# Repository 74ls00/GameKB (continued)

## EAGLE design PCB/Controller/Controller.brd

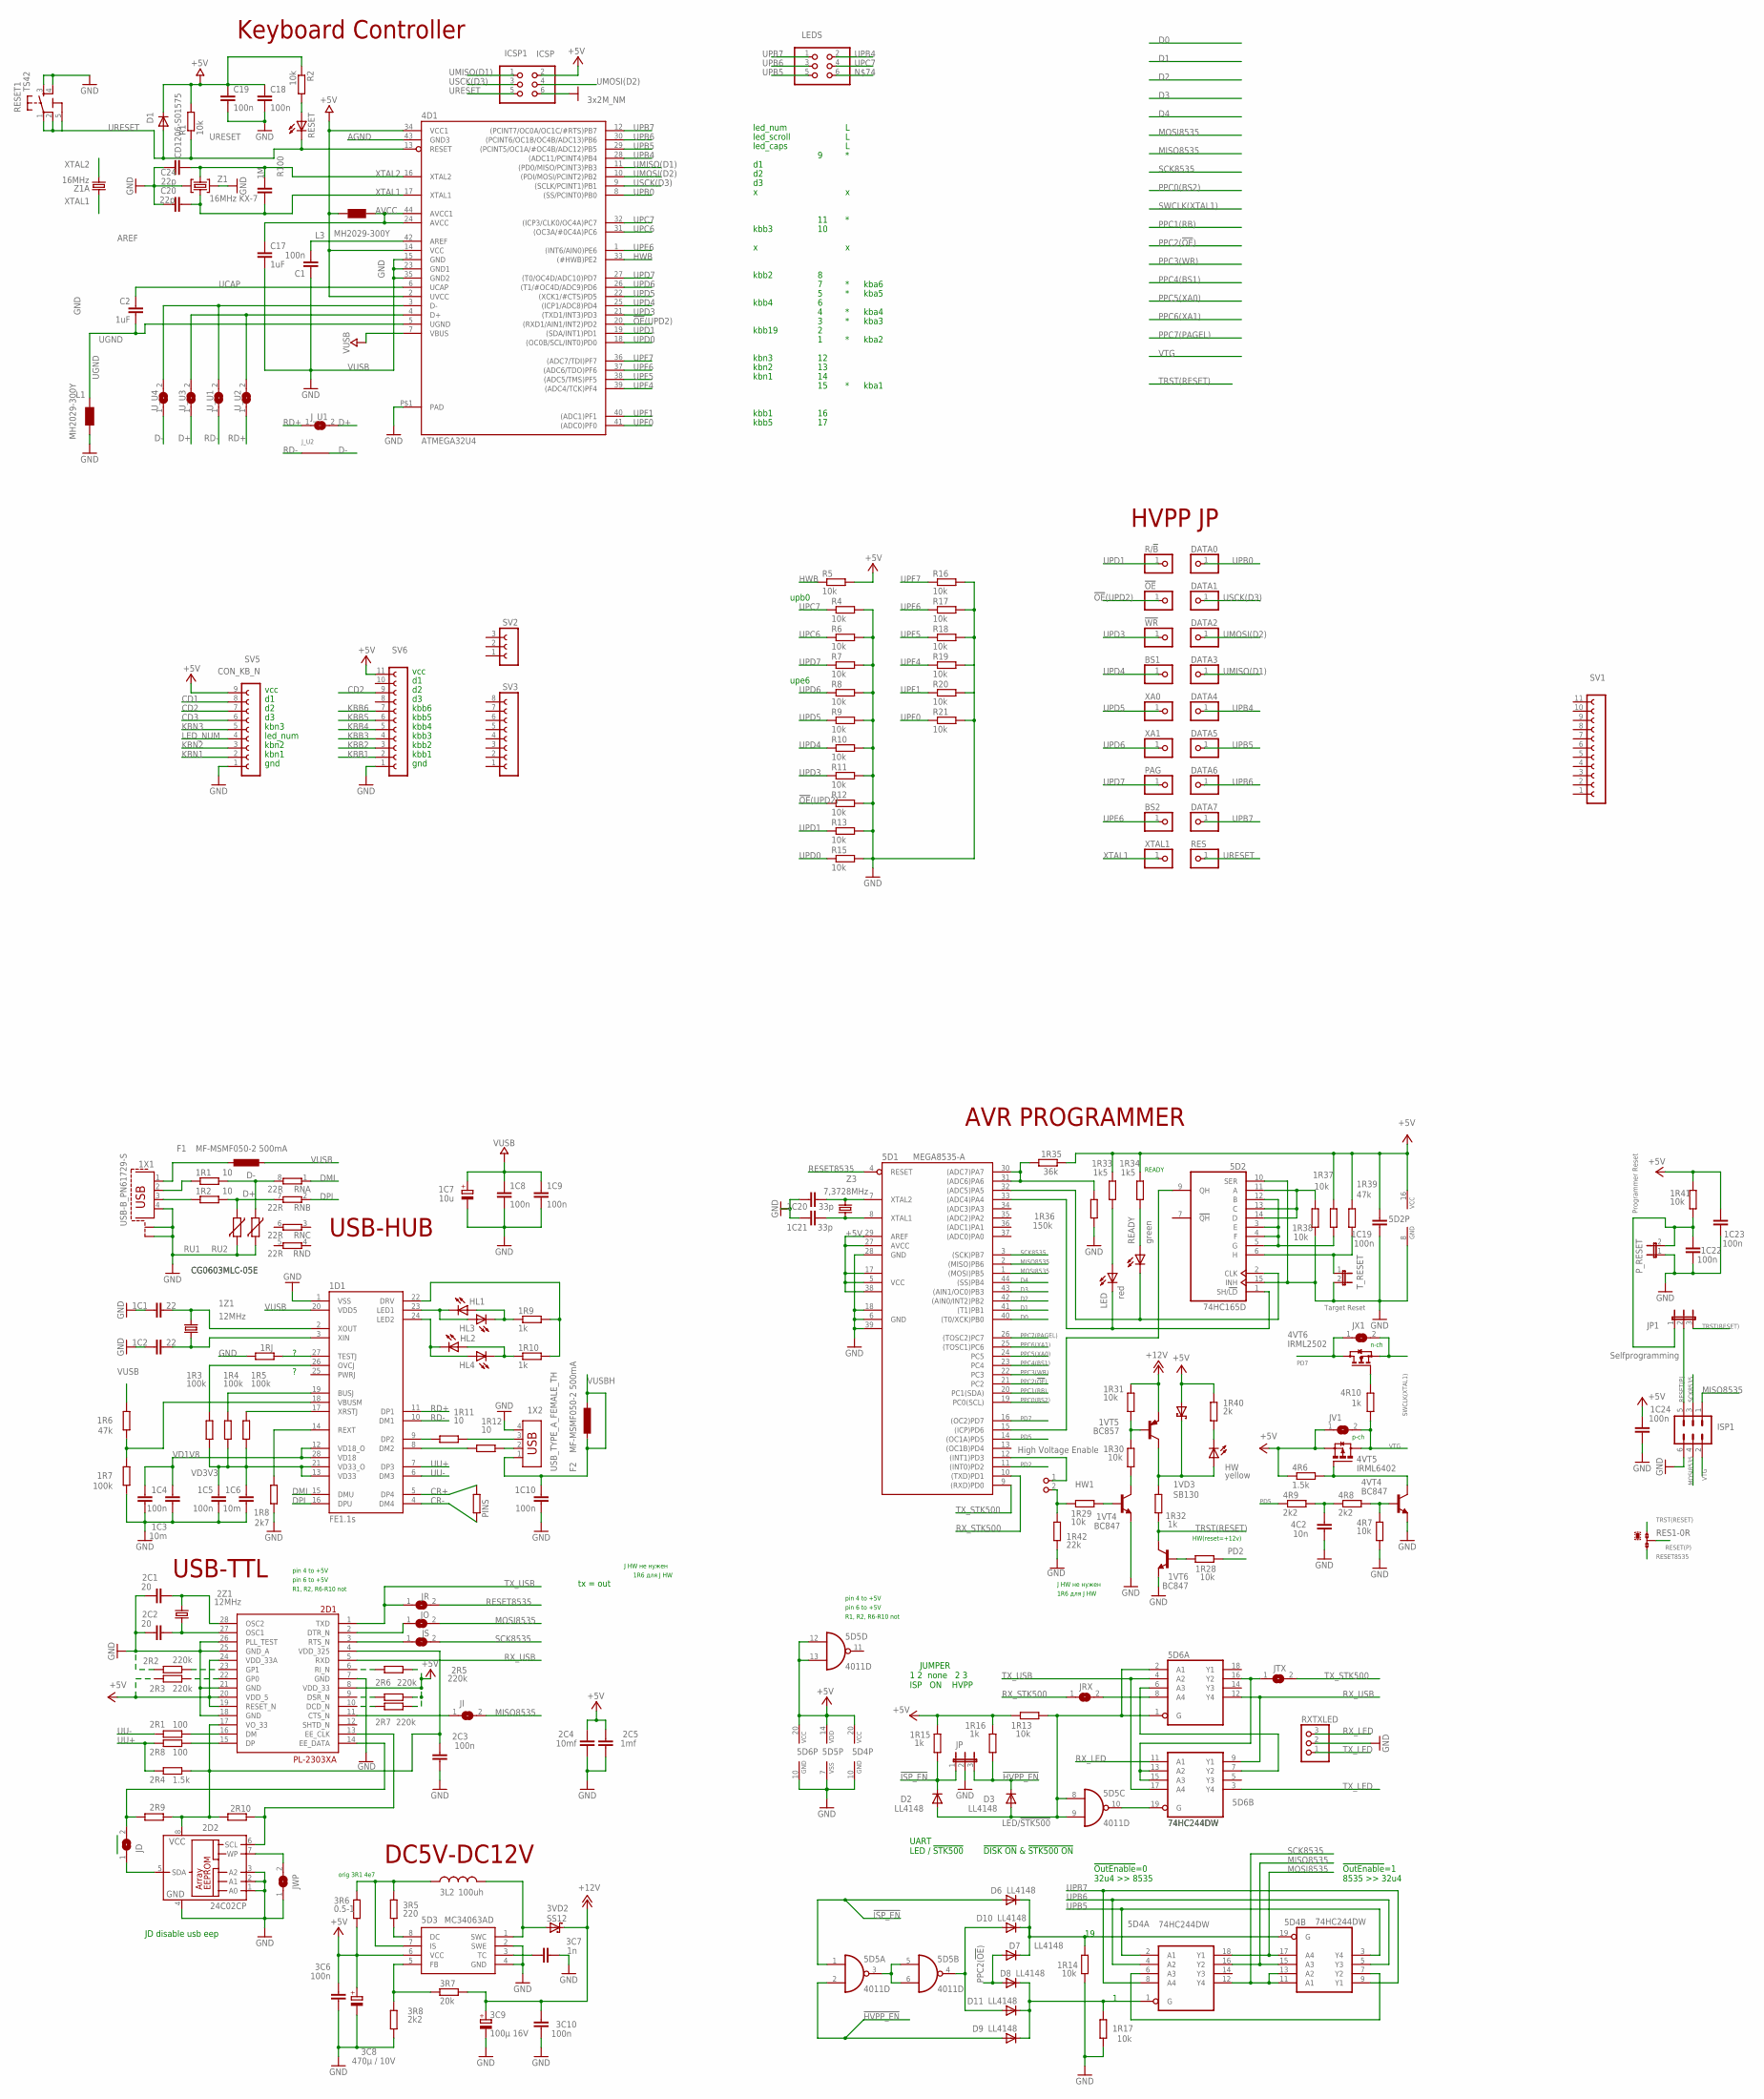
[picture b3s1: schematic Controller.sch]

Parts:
1C1, 1C2: 22; C0603
1C3, 1C6: 10m; C1206
1C4, 1C5, 1C8, 1C9, 1C10, 1C19, 1C22, 1C23, 1C24, 2C3: 100n; C0805
1C7: 10u; SMC_B
1C20, 1C21: 33p; C0805
1D1: FE1.1S; FE1.1S_SSOP-28
1R1, 1R2, 1R11, 1R12: 10; R0603
1R3, 1R4, 1R7: 100k; R0805
1R5: 100k; R1206W
1R6: 47k; R1206W
1R8: 2k7; R0805
1R9, 1R10: 1k; R0805
1R13, 1R14, 1R17, 1R29, 1R30, 1R31, 1R37, 1R38, 1R41, 4R7: 10k; M0805
1R15, 1R16, 1R32, 4R10: 1k; M0805
1R28: 10k; R0805
1R33, 1R34: 1k5; M0805
1R35: 36k; M0805
1R36: 150k; R1206
1R39: 47k; M0805
1R40: 2k; R1206W
1R42: 22k; M1206
1RJ, 2R9, 2R10: R-EU_R0805; R0805
1VD3: SB130; SMB
1VT4, 1VT6, 4VT4: BC847; SOT23
1VT5: BC857; SOT23-BEC
1X1: USB-B_PN61729-S
1X2: USB_TYPE_A_FEMALE_TH
1Z1, 2Z1: 12MHz; HC49/S
2C1, 2C2: 20; C0805
2C4: 10mf; C1210
2C5: 1mf; C0805
2D1: PL-2303XA; SSOP28DB
2D2: 24C02CP; DIL8; MPN 24C02C/P
2R1, 2R8: 100; R0603
2R2, 2R6, 2R7: 220k; R0603
2R3, 2R5: 220k; R1206W
2R4: 1.5k; R0603
3C6: 100n; C025-024X044
3C7: 1n; C025-025X050
3C8: 470µ / 10V; RCL_E3,5-8
3C9: 100µ 16V; RCL_E3,5-8
3C10: 100n; C025-025X050
3L2: 100uh; 0207/10
3R5: 220; R1206
3R6: 0.5-1; M1206
3R7: 20k; M0805
3R8, 4R9: 2k2; M0805
3VD2: SS12; SMB
4C2: 10n; C1206
4D1: ATMEGA32U4; SMARTPRJ_TQFP44-PAD
4R6: 1.5k; M0805
4R8: 2k2; M1206
4VT5: IRML6402; SUPER-SOT3
4VT6: IRML2502; SOT23
5D1: MEGA8535-A; TQFP44
5D2: 74HC165D; SO16
5D3: MC34063AD; SOIC8
5D4, 5D6: 74HC244DW; SO20W
5D5: 4011D; SO14
!OE: PINHD-1X1; 1X01
!WR: PINHD-1X1; 1X01
BS1, BS2: PINHD-1X1; 1X01
C1, C19: 100n; C0603-ROUND
C2: 1uF; C0603
C17: 1uF; C0603-ROUND
C18: 100n; C0603
C20, C24: 22p; C0603
D1: CD1206-S01575; MINIMELF
D2, D3, D6, D7, D8, D9, D10, D11: LL4148; SOD80C
DATA0, DATA1, DATA2, DATA3, DATA4, DATA5, DATA6, DATA7: PINHD-1X1; 1X01
F1, F2: MF-MSMF050-2 500mA; L1812
HL1, HL2, HL3, HL4: LEDSML0603; SML0603
HW: yellow; SML0603
HW1: High Voltage Enable; PINHEAD_1X02
ICSP1: ICSP; 2X03
ISP1: MA03-2
JD: SJ
JI: SJ
JO: SJ
JP: JP2E; JP2
JP1: Selfprogramming; JUMPER_JP2
JR: SJ
JRX: SJ
JS: SJ
JTX: SJ
JV1: SJ
JWP: SJ
JX1: SJ
J_U1: SJ
J_U2: J; R1206W
L1, L3: MH2029-300Y; 0805
LED: red; SML0603
LEDS: PINHD-2X3; 2X03
PAG: PINHD-1X1; 1X01
PINS: R-EU_R0805; R0805
P_RESET: JP1E; JP1
R1, R2, R4, R6, R7, R8, R9, R10, R11, R12, R13, R15, R16, R17, R18, R19, R20, R21: 10k; M0805
R5: 10k; M1206
R100: 1M; C0805
R/!B: PINHD-1X1; 1X01
READY: green; SML0603
RES: PINHD-1X1; 1X01
RES1: 0R-JUMPA; A0R-JMP
RESET: LEDSML0805; SML0805
RESET1: TS42
RN: 22R; CAY16
RU1, RU2: CG0603MLC-05E; CT/CN0603
RXTXLED: PINHD-1X3; 1X03
SV1, SV6: FE12-1; FE12
SV2: FE03-1
SV3: FE08-1; FE08
SV5: CON_KB_N; FE09
T_RESET: JP1E; JP1
U_U1, U_U2, U_U3, U_U4: SJ
XA0, XA1: PINHD-1X1; 1X01
XTAL1: PINHD-1X1; 1X01
Z1: 16MHz KX-7; CRYSTAL-3.2-2.5
Z1A: 16MHz; HC49/S
Z3: 7,3728MHz; HC49U-V

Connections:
3VUSB2: 2C3.1, 2D1.4 (VDD_325), 2D1.17 (VO_33), 2D2.8 (VCC), 2R4.1, 2R9.2, 2R10.2
!HVPP_EN: 1R16.1, 5D5.2 (I1), D3.C, D9.A, JP.3
!ISP_EN: 1R15.1, 5D5.1 (I0), D2.C, D6.A, JP.1
!OE741: 1R17.2, 5D4.1 (G), D8.C, D9.C, D11.C
!OE!(UPD2): 4D1.20 ((RXD1/AIN1/INT2)PD2), !OE.1, R12.1
+5V: 1C19.1, 1C23.2, 1C24.2, 1R13.2, 1R15.2, 1R16.2, 1R33.2, 1R34.2, 1R35.2, 1R37.1, 1R39.1, 1R40.2, 1R41.2, 1VD3.A, 2C4.2, 2C5.2, 2D1.8 (VDD_33), 2D1.19 (RESET_N), 2D1.20 (VDD_5), 2D1.24 (VDD_33A), 2R3.1, 2R5.2, 2R6.1, 2R7.1, 3C6.1, 3C8.+, 3R6.1, 4D1.2 (UVCC), 4D1.14 (VCC), 4D1.34 (VCC1), 4R6.1, 4VT5.2 (S), 5D1.5 (VCC), 5D1.17 (VCC1), 5D1.27 (AVCC), 5D1.29 (AREF), 5D1.38 (VCC2), 5D2.16 (VCC), 5D3.6 (VCC), 5D4.20 (VCC), 5D5.12 (I0), 5D5.13 (I1), 5D5.14 (VDD), 5D6.20 (VCC), C18.1, C19.1, D1.C, ICSP1.2, JV1.1, L3.1, R1.2, R2.1, R5.2, SV5.9, SV6.11
+12V: 1R31.2, 1VT5.E, 3C9.+, 3C10.2, 3R7.2, 3VD2.C
AGND: 4D1.43 (GND3)
AREF: 4D1.42 (AREF), C1.2
AVCC: 4D1.24 (AVCC), 4D1.44 (AVCC1), C17.1, L3.2
CD1: SV5.8
CD2: SV5.7, SV6.9
CD3: SV5.6
CR+: 1D1.5 (DP4), PINS.2
CR-: 1D1.4 (DM4), PINS.1
D0: 5D1.40 ((T0/XCK)PB0)
D1: 5D1.41 ((T1)PB1)
D2: 5D1.42 ((AIN0/INT2)PB2)
D3: 5D1.43 ((AIN1/OC0)PB3)
D4: 5D1.44 ((SS)PB4)
D+: 1R2.2, J_U1.2, RN.7 (2), RU1.1, U_U3.1
D-: 1R1.2, J_U2.1, RN.8 (2), RU2.1, U_U4.1
DMI: 1D1.15 (DMU), RN.1
DPI: 1D1.16 (DPU), RN.2 (1)
GND: 1C1.1, 1C2.1, 1C3.2, 1C4.2, 1C5.2, 1C6.2, 1C7.-, 1C8.1, 1C9.1, 1C10.2, 1C19.2, 1C20.1, 1C21.1, 1C22.1, 1C23.1, 1C24.1, 1D1.1 (VSS), 1R7.1, 1R8.1, 1R14.1, 1R17.1, 1R36.1, 1R38.1, 1R42.1, 1RJ.2, 1VT4.2 (E), 1VT6.2 (E), 1X1.4, 1X1.S1, 1X1.S2, 1X2.4, 2C1.1, 2C2.1, 2C3.2, 2C4.1, 2C5.1, 2D1.7 (GND), 2D1.18 (GND), 2D1.21 (GND), 2D1.25 (GND_A), 2D1.26 (PLL_TEST), 2D2.1 (A0), 2D2.2 (A1), 2D2.3 (A2), 2D2.4 (GND), 2R2.1, 3C6.2, 3C7.2, 3C8.-, 3C9.-, 3C10.1, 3R8.1, 4C2.1, 4D1.15 (GND), 4D1.23 (GND1), 4D1.35 (GND2), 4D1.P$1 (PAD), 4R7.1, 4VT4.2 (E), 5D1.6 (GND), 5D1.18 (GND1), 5D1.28 (GND), 5D1.39 (GND2), 5D2.8 (GND), 5D2.10 (SER), 5D2.15 (INH), 5D3.2 (SWE), 5D3.4 (GND), 5D4.10 (GND), 5D5.7 (VSS), 5D6.10 (GND), C1.1, C17.2, C18.2, C19.2, C20.1, C24.2, ICSP1.6, ISP1.6, JP.2, JWP.1, L1.2, P_RESET.1, R4.2, R6.2, R7.2, R8.2, R9.2, R10.2, R11.2, R12.2, R13.2, R15.2, R16.2, R17.2, R18.2, R19.2, R20.2, R21.2, RESET1.3, RESET1.4, RU1.2, RU2.2, RXTXLED.2, SV5.1, SV6.1, T_RESET.2, Z1.2 (GND), Z1.4 (GND)
HWB: 4D1.33 ((#HWB)PE2), R5.1
ID+: 1R2.1, 1X1.3
ID-: 1R1.1, 1X1.2
KBB1: SV6.2
KBB2: SV6.3
KBB3: SV6.4
KBB4: SV6.5
KBB5: SV6.6
KBB6: SV6.7
KBN1: SV5.2
KBN2: SV5.3
KBN3: SV5.5
LED/!STK500: 1R13.1, 5D5.8 (I0), 5D5.9 (I1), 5D6.1 (G), 5D6.2 (A1), D2.A, D3.A
LED_NUM: SV5.4
MISO8535: 5D1.2 ((MISO)PB6), 5D4.15 (A3), 5D4.16 (Y2), ISP1.1, JI.2
MOSI8535: 5D1.1 ((MOSI)PB5), 5D4.17 (A4), 5D4.18 (Y1), ISP1.4, JO.2
N1: 5D1.33 ((ADC4)PA4), 5D2.1 (SH/!LD), LED.C
unnamed: 5D5.10 (O), 5D6.19 (G)
unnamed: R2.2, RESET.A
unnamed: 5D4.6 (A3), 5D4.7 (Y2)
unnamed: 1D1.9 (DP2), 1R11.1
unnamed: 1D1.8 (DM2), 1R12.1
unnamed: 1X1.1, F1.2
unnamed: 1C1.2, 1D1.2 (XOUT), 1Z1.1
unnamed: 1C2.2, 1D1.3 (XIN), 1Z1.2
unnamed: 1D1.17 (XRSTJ), 1R5.2
unnamed: 1D1.22 (DRV), 1R9.2, 1R10.2
unnamed: 1R11.2, 1X2.3
unnamed: 1R12.2, 1X2.2
unnamed: 1D1.23 (LED1), HL1.C, HL3.A
unnamed: 1D1.19 (BUSJ), 1R4.2
unnamed: 1D1.18 (VBUSM), 1R6.1, 1R7.2
unnamed: 1D1.24 (LED2), HL2.C, HL4.A
unnamed: 1R10.1, HL2.A, HL4.C
unnamed: 1D1.26 (OVCJ), 1R3.2
unnamed: 4D1.4 (D+), U_U2.2, U_U3.2
unnamed: 1D1.14 (REXT), 1R8.2
unnamed: 5D6.13 (A2), 5D6.15 (A3), 5D6.16 (Y2), JTX.1
unnamed: 1D1.27 (TESTJ), 1RJ.1
unnamed: 5D6.8 (A4), JRX.2
unnamed: 4D1.3 (D-), U_U1.2, U_U4.2
unnamed: 5D6.6 (A3), 5D6.7 (Y2)
unnamed: 2D2.5 (SDA), JD.1
unnamed: 1R34.1, READY.A
unnamed: 5D5.3 (O), 5D5.5 (I0), 5D5.6 (I1)
unnamed: 1R9.1, HL1.A, HL3.C
unnamed: 1R35.1, 1R36.2, 5D1.30 ((ADC7)PA7), 5D1.31 ((ADC6)PA6)
unnamed: 5D1.32 ((ADC5)PA5), 5D2.2 (CLK), READY.C
unnamed: 1R39.2, 5D2.6 (H), T_RESET.1
unnamed: 5D1.12 ((INT1)PD3), HW1.1
unnamed: 1R29.2, 1R42.2, HW1.2
unnamed: 2D2.7 (WP), JWP.2
unnamed: 1R32.2, 1VD3.C, 1VT5.C, HW.A
unnamed: 1R29.1, 1VT4.1 (B)
unnamed: 1R14.2, 5D4.19 (G), D6.C, D7.C, D10.C
unnamed: 1R30.1, 1VT4.3 (C)
unnamed: 1R30.2, 1R31.1, 1VT5.B
unnamed: 5D1.15 ((ICP)PD6), 5D2.9 (QH)
unnamed: 1R33.1, LED.A
unnamed: 1R38.2, 5D2.11 (A), 5D2.13 (C), 5D2.14 (D)
unnamed: 2D1.15 (DP), 2R8.2
unnamed: 2D1.16 (DM), 2R1.2
unnamed: 2D1.23 (GP1), 2R2.2
unnamed: 2D1.22 (GP0), 2R3.2
unnamed: 2C1.2, 2D1.28 (OSC2), 2Z1.2
unnamed: 2C2.2, 2D1.27 (OSC1), 2Z1.1
unnamed: 2D1.6 (RI_N), 2R5.1
unnamed: 2D1.9 (DSR_N), 2R6.2
unnamed: 2D1.10 (DCD_N), 2R7.2
unnamed: 2D1.11 (CTS_N), JI.1
unnamed: 2D1.3 (RTS_N), JS.1
unnamed: 2D1.2 (DTR_N), JO.1
unnamed: 1R37.2, 5D2.3 (E), 5D2.4 (F), 5D2.5 (G), 5D2.12 (B)
unnamed: 2D1.14 (EE_DATA), 2R9.1, JD.2
unnamed: 2D1.13 (EE_CLK), 2D2.6 (SCL), 2R10.1
unnamed: 1R28.2, 1VT6.1 (B)
unnamed: 3R5.1, 5D3.8 (DC)
unnamed: 3L2.1, 3R5.2, 3R6.2, 5D3.7 (IS)
unnamed: 5D5.4 (O), D10.A, D11.A
unnamed: 3R7.1, 3R8.2, 5D3.5 (FB)
unnamed: 3L2.2, 3VD2.A, 5D3.1 (SWC)
unnamed: 3C7.1, 5D3.3 (TC)
unnamed: 1C20.2, 5D1.7 (XTAL2), Z3.2
unnamed: 1C21.2, 5D1.8 (XTAL1), Z3.1
unnamed: 4R6.2, 4VT4.3 (C), 4VT5.1 (G)
unnamed: 4R7.2, 4R8.2, 4VT4.1 (B)
unnamed: 4C2.2, 4R8.1, 4R9.2
unnamed: 1R40.1, HW.C
unnamed: 4R10.2, 4VT6.1 (G)
PD2: 1R28.1, 5D1.11 ((INT0)PD2)
PD5: 4R9.1, 5D1.14 ((OC1A)PD5)
PD7: 4VT6.3 (D), 5D1.16 ((OC2)PD7), JX1.1
PPC0(BS2): 5D1.19 (PC0(SCL))
PPC1(RB): 5D1.20 (PC1(SDA))
PPC2(!OE!): 5D1.21 (PC2), D7.A, D8.A
PPC3(WR): 5D1.22 (PC3)
PPC4(BS1): 5D1.23 (PC4)
PPC5(XA0): 5D1.24 (PC5)
PPC6(XA1): 5D1.25 ((TOSC1)PC6)
PPC7(PAGEL): 5D1.26 ((TOSC2)PC7)
RD+: 1D1.11 (DP1), J_U1.1, U_U2.1
RD-: 1D1.10 (DM1), J_U2.2, U_U1.1
RESET8535: 1C22.2, 1R41.1, 5D1.4 (RESET), JP1.1, JR.2, P_RESET.2, RES1.3
RESET(P): ISP1.5, JP1.2, RES1.2
RX_LED: 5D6.11 (A1), RXTXLED.3
RX_STK500: 5D1.10 ((TXD)PD1), JRX.1
RX_USB: 2D1.5 (RXD), 5D6.9 (Y1), 5D6.12 (Y4)
SCK8535: 5D1.3 ((SCK)PB7), 5D4.11 (A1), 5D4.12 (Y4), 5D4.13 (A2), ISP1.3, JS.2
SWCLK(XTAL1): 4VT6.2 (S), JX1.2
TRST(RESET): 1R32.1, 1VT6.3 (C), JP1.3, RES1.1
TX_LED: 5D6.3 (Y4), RXTXLED.1
TX_STK500: 5D1.9 ((RXD)PD0), JTX.2
TX_USB: 2D1.1 (TXD), 5D6.4 (A2), 5D6.17 (A4), JR.1
UCAP: 4D1.6 (UCAP), C2.1
UGND: 4D1.5 (UGND), C2.2, L1.1
UMISO(D1): 4D1.11 ((PD0/MISO/PCINT3)PB3), DATA3.1, ICSP1.1
UMOSI(D2): 4D1.10 ((PDI/MOSI/PCINT2)PB2), DATA2.1, ICSP1.4
UPB0: 4D1.8 ((SS/PCINT0)PB0), DATA0.1
UPB4: 4D1.28 ((ADC11/PCINT4)PB4), DATA4.1, LEDS.2
UPB5: 4D1.29 ((PCINT5/OC1A/#OC4B/ADC12)PB5), 5D4.2 (A1), 5D4.3 (Y4), DATA5.1, LEDS.5
UPB6: 4D1.30 ((PCINT6/OC1B/OC4B/ADC13)PB6), 5D4.4 (A2), 5D4.5 (Y3), DATA6.1, LEDS.3
UPB7: 4D1.12 ((PCINT7/OC0A/OC1C/#RTS)PB7), 5D4.8 (A4), 5D4.9 (Y1), DATA7.1, LEDS.1
UPC6: 4D1.31 ((OC3A/#0C4A)PC6), R6.1
UPC7: 4D1.32 ((ICP3/CLK0/OC4A)PC7), LEDS.4, R4.1
UPD0: 4D1.18 ((OC0B/SCL/INT0)PD0), R15.1
UPD1: 4D1.19 ((SDA/INT1)PD1), R13.1, R/!B.1
UPD3: 4D1.21 ((TXD1/INT3)PD3), !WR.1, R11.1
UPD4: 4D1.25 ((ICP1/ADC8)PD4), BS1.1, R10.1
UPD5: 4D1.22 ((XCK1/#CTS)PD5), R9.1, XA0.1
UPD6: 4D1.26 ((T1/#OC4D/ADC9)PD6), R8.1, XA1.1
UPD7: 4D1.27 ((T0/OC4D/ADC10)PD7), PAG.1, R7.1
UPE6: 4D1.1 ((INT6/AIN0)PE6), BS2.1
UPF0: 4D1.41 ((ADC0)PF0), R21.1
UPF1: 4D1.40 ((ADC1)PF1), R20.1
UPF4: 4D1.39 ((ADC4/TCK)PF4), R19.1
UPF5: 4D1.38 ((ADC5/TMS)PF5), R18.1
UPF6: 4D1.37 ((ADC6/TDO)PF6), R17.1
UPF7: 4D1.36 ((ADC7/TDI)PF7), R16.1
URESET: 4D1.13 (RESET), D1.A, ICSP1.5, R1.1, RES.1, RESET.C, RESET1.1, RESET1.2, RESET1.5 (5-GND)
USCK(D3): 4D1.9 ((SCLK/PCINT1)PB1), DATA1.1, ICSP1.3
UU+: 1D1.7 (DP3), 2R4.2, 2R8.1
UU-: 1D1.6 (DM3), 2R1.1
VD1V8: 1C3.1, 1C4.1, 1D1.12 (VD18_O), 1D1.28 (VD18)
VD3V3: 1C5.1, 1C6.1, 1D1.13 (VD33), 1D1.21 (VD33_O), 1R3.1, 1R4.1, 1R5.1
VTG: 4R10.1, 4VT5.3 (D), ISP1.2, JV1.2
VUSB: 1C7.+, 1C8.2, 1C9.2, 1D1.20 (VDD5), 1R6.2, 4D1.7 (VBUS), F1.1
VUSBH: 1C10.1, 1X2.1, F2.1, F2.2
XTAL1: 4D1.17 (XTAL1), C20.2, R100.2, XTAL1.1, Z1.3 (C2), Z1A.2
XTAL2: 4D1.16 (XTAL2), C24.1, R100.1, Z1.1 (C1), Z1A.1

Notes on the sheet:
kbn1
kbn2
kbn3
led_num
kbb1
kbb2
kbb3
kbb4
kbb5
kbb6
gnd
vcc
pin 4 to +5V
R1, R2, R6-R10 not
pin 6 to +5V
J HW не нужен
1R6 для J HW
USB-HUB
kbb19
led_caps
led_scroll
USB-TTL
Target Reset
Programmer Reset
orig 3R1 4e7
HW(reset=+12v)
READY
n-ch
p-ch
HVPP JP
upe6
upb0
kba1
kba2
kba3
kba4
kba5
kba6
DC5V-DC12V
!DISK ON! & !STK500 ON

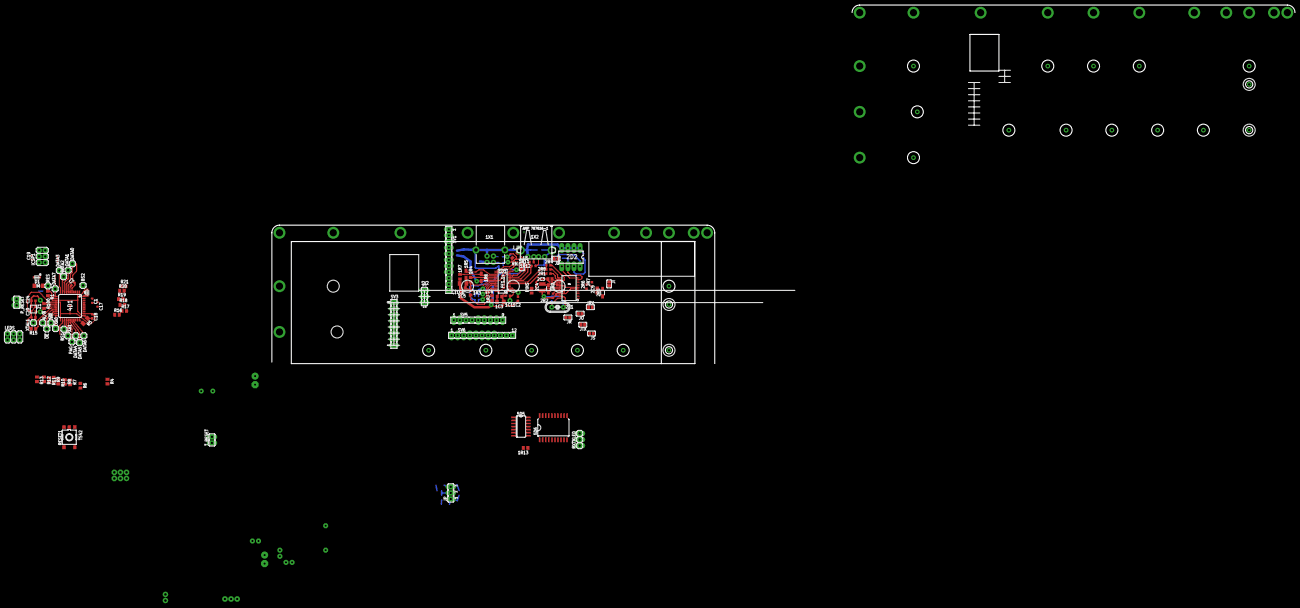
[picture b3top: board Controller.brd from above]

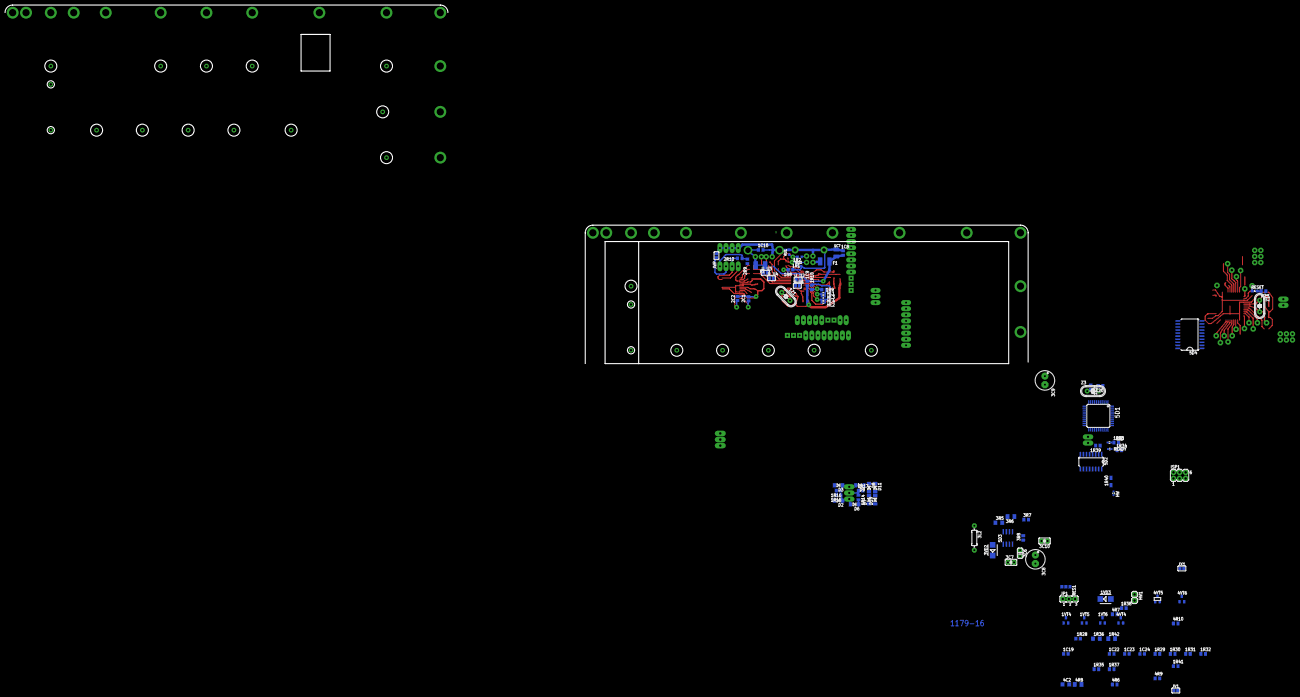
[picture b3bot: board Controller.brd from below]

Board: 2 copper layers, 208 parts (94 on the bottom side), 149 nets.

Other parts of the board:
U$3: U235

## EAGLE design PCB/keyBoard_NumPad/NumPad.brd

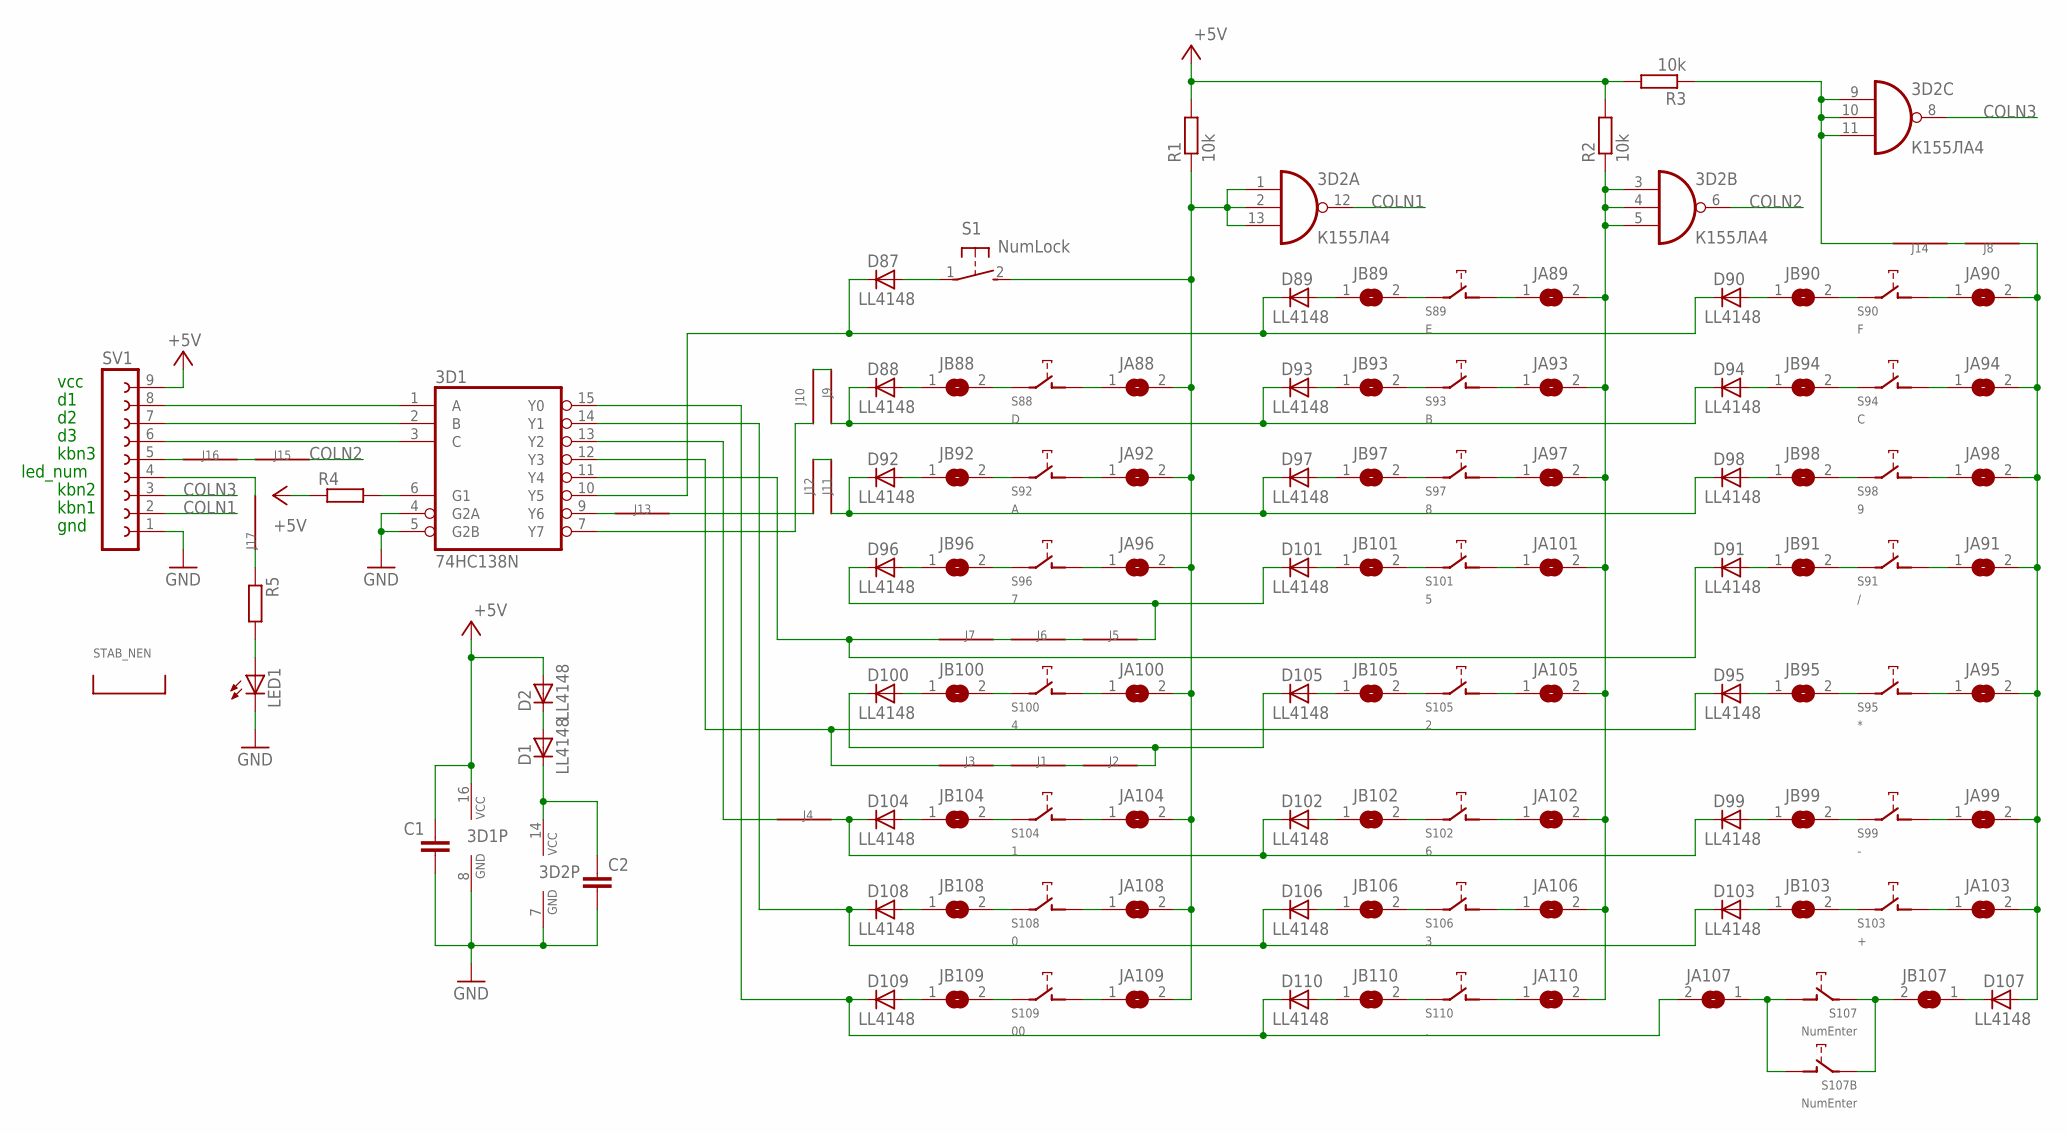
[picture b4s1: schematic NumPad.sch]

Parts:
3D1: 74HC138N; DIL16
3D2: К155ЛА4; DIL14
C1, C2: C-EUC1206; C1206
D1, D2, D87, D88, D89, D90, D91, D92, D93, D94, D95, D96, D97, D98, D99, D100, D101, D102, D103, D104, D105, D106, D107, D108, D109, D110: LL4148; SOD80C
J1, J2, J3, J4, J5, J6, J7, J8, J9, J10, J11, J12, J13, J14, J15, J16, J17: J; R1206W
JA88, JA89, JA90, JA91, JA92, JA93, JA94, JA95, JA96, JA97, JA98, JA99, JA100, JA101, JA102, JA103, JA104, JA105, JA106, JA107, JA108, JA109, JA110: SJ
JB88, JB89, JB90, JB91, JB92, JB93, JB94, JB95, JB96, JB97, JB98, JB99, JB100, JB101, JB102, JB103, JB104, JB105, JB106, JB107, JB108, JB109, JB110: SJ
LED1: LED5MM
R1, R2, R3: 10k; R1206W
R4, R5: R-EU_R1206W; R1206W
S1: NumLock; B3F-31XX
S88: D; CHERRY-MX-4P
S89: E; CHERRY-MX-4P
S90: F; CHERRY-MX-4P
S91: /; CHERRY-MX-4P
S92: A; CHERRY-MX-4P
S93: B; CHERRY-MX-4P
S94: C; CHERRY-MX-4P
S95: *; CHERRY-MX-4P
S96: 7; CHERRY-MX-4P
S97: 8; CHERRY-MX-4P
S98: 9; CHERRY-MX-4P
S99: -; CHERRY-MX-4P
S100: 4; CHERRY-MX-4P
S101: 5; CHERRY-MX-4P
S102: 6; CHERRY-MX-4P
S103: +; CHERRY-MX-4P
S104: 1; CHERRY-MX-4P
S105: 2; CHERRY-MX-4P
S106: 3; CHERRY-MX-4P
S107, S107B: NumEnter; CHERRY-MX-4P
S108: 0; CHERRY-MX-4P
S109: 00; CHERRY-MX-4P
S110: .; CHERRY-MX-4P
STAB_NEN: STAB; ZEALIOS-PCB_2U
SV1: FE09-1; FE09

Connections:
+5V: 3D1.16 (VCC), C1.1, D2.A, R1.2, R2.2, R3.2, R4.1, SV1.9
COLN1: 3D2.12 (O), SV1.2
COLN2: 3D2.6 (O), J15.1
COLN3: 3D2.8 (O), SV1.3
GND: 3D1.4 (G2A), 3D1.5 (G2B), 3D1.8 (GND), 3D2.7 (GND), C1.2, C2.2, LED1.K (C), SV1.1
unnamed: D92.C, D97.C, D98.C, J11.2
unnamed: D100.C, D105.C, J2.1
unnamed: D107.C, JB107.1
unnamed: J1.2, J3.1
unnamed: J1.1, J2.2
unnamed: 3D1.1 (A), SV1.8
unnamed: 3D2.3 (I0), 3D2.4 (I1), 3D2.5 (I2), JA89.2, JA93.2, JA97.2, JA101.2, JA102.2, JA105.2, JA106.2, JA110.2, R2.1
unnamed: 3D1.2 (B), SV1.7
unnamed: D99.C, D102.C, D104.C, J4.1
unnamed: 3D1.3 (C), SV1.6
unnamed: 3D1.13 (Y2), J4.2
unnamed: D96.C, D101.C, J5.1
unnamed: J6.2, J7.1
unnamed: 3D2.1 (I0), 3D2.2 (I1), 3D2.13 (I2), JA88.2, JA92.2, JA96.2, JA100.2, JA104.2, JA108.2, JA109.2, R1.1, S1.2 (S)
unnamed: J5.2, J6.1
unnamed: D88.C, D93.C, D94.C, J9.2
unnamed: 3D2.9 (I0), 3D2.10 (I1), 3D2.11 (I2), J14.1, R3.1
unnamed: 3D1.7 (Y7), J10.1
unnamed: J9.1, J10.2
unnamed: J11.1, J12.1
unnamed: J12.2, J13.1
unnamed: D107.A, J8.2, JA90.2, JA91.2, JA94.2, JA95.2, JA98.2, JA99.2, JA103.2
unnamed: 3D1.9 (Y6), J13.2
unnamed: 3D1.6 (G1), R4.2
unnamed: J8.1, J14.2
unnamed: LED1.A, R5.2
unnamed: J16.2, SV1.5
unnamed: J15.2, J16.1
unnamed: J17.2, SV1.4
unnamed: J17.1, R5.1
unnamed: 3D1.10 (Y5), D87.C, D89.C, D90.C
unnamed: 3D1.11 (Y4), D91.C, J7.2
unnamed: 3D1.12 (Y3), D95.C, J3.2
unnamed: 3D1.14 (Y1), D103.C, D106.C, D108.C
unnamed: D1.A, D2.C
unnamed: 3D2.14 (VCC), C2.1, D1.C
unnamed: JA107.1, S107.SW2 (PIN-2), S107B.SW2 (PIN-2)
unnamed: D104.A, JB104.1
unnamed: D87.A, S1.1
unnamed: D88.A, JB88.1
unnamed: JB88.2, S88.SW1 (PIN-1)
unnamed: JA88.1, S88.SW2 (PIN-2)
unnamed: D89.A, JB89.1
unnamed: JB89.2, S89.SW1 (PIN-1)
unnamed: JA89.1, S89.SW2 (PIN-2)
unnamed: D90.A, JB90.1
unnamed: JB90.2, S90.SW1 (PIN-1)
unnamed: JA90.1, S90.SW2 (PIN-2)
unnamed: D91.A, JB91.1
unnamed: JB91.2, S91.SW1 (PIN-1)
unnamed: JA91.1, S91.SW2 (PIN-2)
unnamed: JB92.2, S92.SW1 (PIN-1)
unnamed: D92.A, JB92.1
unnamed: JA92.1, S92.SW2 (PIN-2)
unnamed: JA93.1, S93.SW2 (PIN-2)
unnamed: JB93.2, S93.SW1 (PIN-1)
unnamed: D93.A, JB93.1
unnamed: D94.A, JB94.1
unnamed: JB94.2, S94.SW1 (PIN-1)
unnamed: JA94.1, S94.SW2 (PIN-2)
unnamed: D95.A, JB95.1
unnamed: JB95.2, S95.SW1 (PIN-1)
unnamed: JA95.1, S95.SW2 (PIN-2)
unnamed: D96.A, JB96.1
unnamed: JB96.2, S96.SW1 (PIN-1)
unnamed: JA96.1, S96.SW2 (PIN-2)
unnamed: JB97.2, S97.SW1 (PIN-1)
unnamed: JA97.1, S97.SW2 (PIN-2)
unnamed: D97.A, JB97.1
unnamed: D98.A, JB98.1
unnamed: JB98.2, S98.SW1 (PIN-1)
unnamed: JA98.1, S98.SW2 (PIN-2)
unnamed: D99.A, JB99.1
unnamed: JB99.2, S99.SW1 (PIN-1)
unnamed: JA99.1, S99.SW2 (PIN-2)
unnamed: D100.A, JB100.1
unnamed: JB100.2, S100.SW1 (PIN-1)
unnamed: JA100.1, S100.SW2 (PIN-2)
unnamed: JB101.2, S101.SW1 (PIN-1)
unnamed: D101.A, JB101.1
unnamed: JA101.1, S101.SW2 (PIN-2)
unnamed: D102.A, JB102.1
unnamed: JB102.2, S102.SW1 (PIN-1)
unnamed: JA102.1, S102.SW2 (PIN-2)
unnamed: D103.A, JB103.1
unnamed: JB103.2, S103.SW1 (PIN-1)
unnamed: JA103.1, S103.SW2 (PIN-2)
unnamed: JB107.2, S107.SW1 (PIN-1), S107B.SW1 (PIN-1)
unnamed: JB104.2, S104.SW1 (PIN-1)
unnamed: JA104.1, S104.SW2 (PIN-2)
unnamed: JB105.2, S105.SW1 (PIN-1)
unnamed: D105.A, JB105.1
unnamed: JA105.1, S105.SW2 (PIN-2)
unnamed: D106.A, JB106.1
unnamed: JB106.2, S106.SW1 (PIN-1)
unnamed: JA106.1, S106.SW2 (PIN-2)
unnamed: JB108.2, S108.SW1 (PIN-1)
unnamed: JA108.1, S108.SW2 (PIN-2)
unnamed: D108.A, JB108.1
unnamed: JB109.2, S109.SW1 (PIN-1)
unnamed: D109.A, JB109.1
unnamed: JA109.1, S109.SW2 (PIN-2)
unnamed: D110.A, JB110.1
unnamed: JB110.2, S110.SW1 (PIN-1)
unnamed: JA110.1, S110.SW2 (PIN-2)
SCK: 3D1.15 (Y0), D109.C, D110.C, JA107.2

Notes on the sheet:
kbn1
kbn2
kbn3
gnd
led_num
vcc
